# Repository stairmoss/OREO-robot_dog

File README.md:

# OREO – ROS Based Quadruped Robot Dog

# OREO V2 – ROS Powered Vision-Based Quadruped Robot  
### Hack Club Advanced Robotics Project

OREO V2 is a next-generation quadruped robot dog powered by a Raspberry Pi 4 and Teensy microcontroller, upgraded from the original ESP32 version into a full ROS-based intelligent robotic platform.

This version adds:

- 🧠 Computer Vision
- 🐾 12 High-Torque (20kg) Servos
- 🤖 ROS 2 Architecture
- 📡 Behavior-Based Control System
- ❤️ Touch Interaction
- 📷 Person Detection & Following

OREO V2 is no longer just a walking robot — it is an intelligent robotic companion platform built under a constrained $395 budget.

---

# 📌 Project Overview

| Item | Description |
|------|-------------|
| Robot Type | Quadruped (4-legged) |
| Architecture | ROS 2 Modular System |
| Main Computer | Raspberry Pi 4 Model B (4GB) |
| Motor Controller | Teensy Microcontroller |
| Servos per Leg | 3 (Hip, Upper, Knee) |
| Total Servos | 12 × 20kg High Torque |
| Sensors | IMU + Touch Sensor + Camera |
| Frame | 3D Printed Spot Micro Style |
| Power | 2S/3S Li-ion / LiPo Battery |
| Budget | ~$395 USD |
| Difficulty | Intermediate → Advanced |

---

# 🎯 Vision & Purpose

OREO V2 was built to:

- Transition from beginner robotics to ROS-based research structure
- Integrate computer vision into a quadruped platform
- Maintain affordability under strict budget constraints
- Build a modular robotic system expandable to SLAM and AI
- Learn real robotics engineering workflow

This robot is designed as a stepping stone toward advanced robotic systems.

---

# 🧠 System Architecture

OREO V2 uses a layered robotics architecture.

## 🔵 High-Level Control (Raspberry Pi 4)

Runs:

- Ubuntu 22.04 (64-bit)
- ROS 2 Humble
- OpenCV
- Behavior Node
- Gait Controller Node
- Vision Node

Responsibilities:

- Computer vision
- State machine decisions
- Gait generation
- Touch reaction logic
- Serial communication with Teensy

---

## 🟢 Low-Level Control (Teensy)

Responsibilities:

- Servo PWM generation via PCA9685
- Reading IMU data
- Executing joint commands
- Sending feedback (IMU + joint states)

Communication via USB Serial to Raspberry Pi.

---

# 🤖 ROS Node Structure

## 1️⃣ teensy_interface_node
- Converts ROS messages to serial packets
- Publishes:
  - `/joint_states`
  - `/imu`
- Subscribes:
  - `/joint_targets`

---

## 2️⃣ gait_controller_node
- Generates walking/trot gait
- Uses IMU feedback for balance correction
- Publishes `/joint_targets`

---

## 3️⃣ vision_node
- Captures camera feed
- Runs OpenCV person detection
- Publishes:
  - `/person_detected`
  - `/target_direction`

---

## 4️⃣ behavior_node (Robot Brain)

Handles states:

- IDLE
- SEARCH
- FOLLOW
- SIT
- HAPPY
- LOW_BATTERY

Input:
- Vision topic
- Touch topic
- Battery monitoring

Output:
- `/cmd_gait`
- Emotion state commands

---

## 5️⃣ touch_node
Reads capacitive or pressure sensor  
Publishes `/touch_event`  

When touched → Robot enters HAPPY state.

---

# ✨ Features

- 🐕 Full 12 DOF quadruped
- ⚙️ 20kg high torque servos
- 📷 Real-time person detection
- 🚶 Follow-human functionality
- ❤️ Touch-based interaction
- 📐 IMU-based balance correction
- 🔋 Dedicated high-current servo rail
- 🧩 Modular ROS architecture
- 🔌 Teensy real-time motor control
- 🧠 AI-expandable platform

---

# 🧩 Mechanical Design

Based on improved Spot Micro style frame.

## Body
- Central frame housing electronics
- Battery compartment protected
- Ventilation for Raspberry Pi
- Camera mount on head

## Legs
- 3 DOF per leg
- Parallel linkage for better weight distribution
- Reinforced servo mounts for 20kg servos
- Proper torque alignment to reduce mechanical stress

---

# 🔋 Power System

- 2S or 3S Li-ion pack
- High-current BEC or buck converter for servos (6V recommended)
- Separate regulated 5V rail for Raspberry Pi

⚠ Always:
- Measure voltage before connecting servos
- Test load voltage drop
- Never power servos directly from Raspberry Pi

---

# 🛠 Assembly Workflow

## Step 1 – 3D Print Parts
- Body frame
- Leg assemblies (×4)
- Head mount
- Internal mounting brackets

## Step 2 – Mount Servos
- Center all 12 servos before installation
- Attach horns at neutral 90°
- Secure using metal gears and lock screws

## Step 3 – Install Electronics
- Mount Raspberry Pi
- Mount Teensy
- Connect PCA9685
- Connect IMU
- Install touch sensor on head/body

## Step 4 – Wiring
- Servo power rail separated
- Signal wires routed cleanly
- Verify ground common between Teensy & Pi

## Step 5 – Software Setup
- Install Ubuntu on Pi
- Install ROS 2
- Clone project repository
- Build workspace using colcon
- Flash Teensy firmware
- Connect via USB

## Step 6 – Calibration
- Zero joint angles
- Adjust trim offsets
- Test single leg motion
- Test gait without load
- Then test full body

---

# 📦 Bill of Materials (Approx Budget)

| Component | Qty |
|-----------|-----|
| Raspberry Pi 4 (4GB) | 1 |
| Teensy Microcontroller | 1 |
| PCA9685 Servo Driver | 1 |
| 20kg Metal Gear Servos | 12 |
| IMU Sensor | 1 |
| Camera Module | 1 |
| Touch Sensor | 1 |
| Battery Pack | 1 |
| Buck Converter | 1 |
| 3D Printed Parts | 1 Set |
| Screws & Inserts | Set |

Total Estimated Cost: ~$390–395 USD

---

# 🚀 Software Capabilities

Current:

- Basic walk
- Trot gait
- Person detection
- Follow mode
- Touch reaction mode

Future Upgrades:

- SLAM
- Obstacle detection
- AI voice recognition
- Depth camera integration
- Web dashboard control

---

# 🏁 What Makes OREO V2 Special

- Built under strict budget
- Uses ROS (research-level framework)
- Integrates vision and behavior logic
- Maintains affordable hardware
- Fully modular and expandable
- Combines mechanical + electrical + software engineering

OREO V2 is not just a robot dog.

It is a robotics learning platform engineered for serious development while staying budget-conscious.

---

---

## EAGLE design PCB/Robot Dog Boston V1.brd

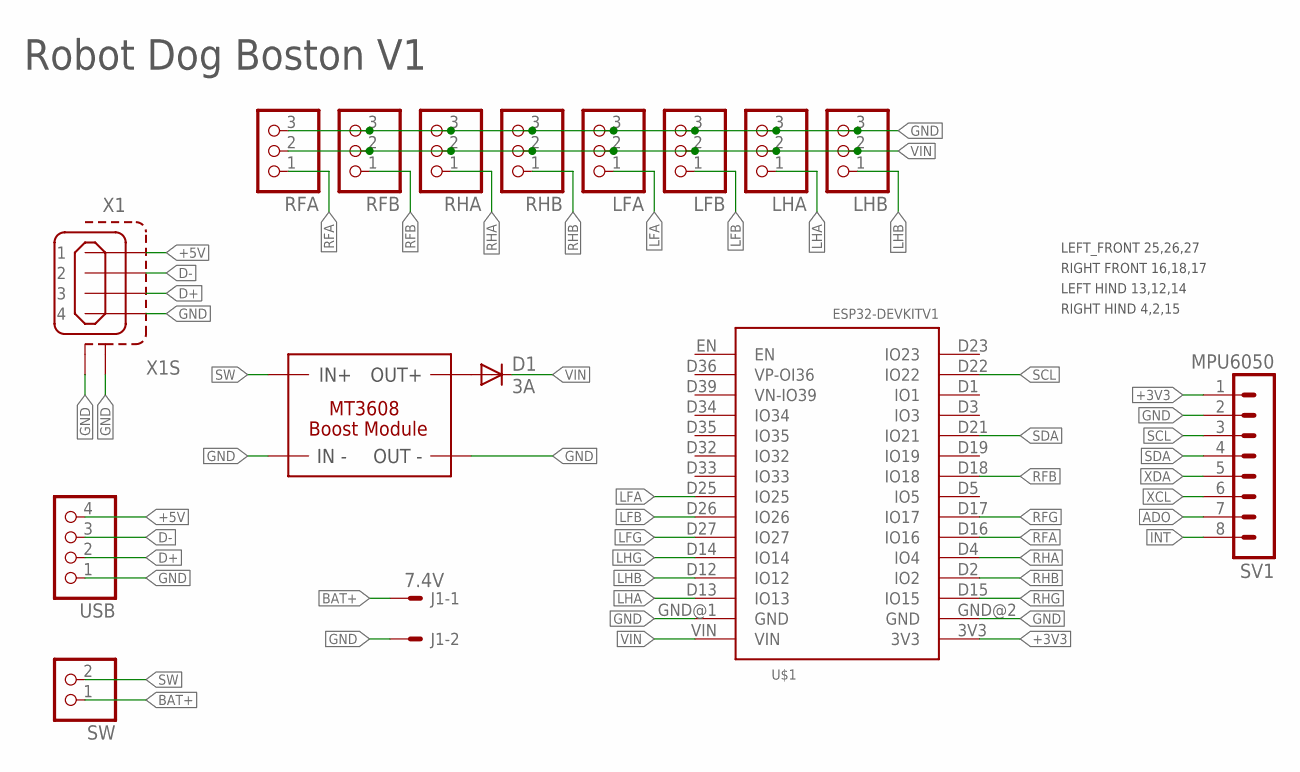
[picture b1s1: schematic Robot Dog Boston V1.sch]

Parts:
D1: 3A; DO15-12
J1: 7.4V; 7395-02
LFA: PINHD-1X3; 1X03
LFB: PINHD-1X3; 1X03
LHA: PINHD-1X3; 1X03
LHB: PINHD-1X3; 1X03
RFA: PINHD-1X3; 1X03
RFB: PINHD-1X3; 1X03
RHA: PINHD-1X3; 1X03
RHB: PINHD-1X3; 1X03
SV1: MPU6050; MA08-1
SW: PINHD-1X2; 1X02
U$1: ESP32DEVKITV1S; ESP32-DEVKIT1S
U$2: REGULATOR_MICRO15.4X9.4; 5V_REGULATOR_BOARD_MICRO_15_4_X_9_4
USB: PINHD-1X4/90; 1X04/90
X1: MINI-USB_SHIELD4P-85-32004-00X; 85-32004-00X

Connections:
+3V3: SV1.1, U$1.3V3
+5V: USB.4, X1.1
ADO: SV1.7
BAT+: J1.1, SW.1
D+: USB.2, X1.3
D-: USB.3, X1.2
GND: J1.2, LFA.3, LFB.3, LHA.3, LHB.3, RFA.3, RFB.3, RHA.3, RHB.3, SV1.2, U$1.GND@1 (GND), U$1.GND@2 (GND), U$2.IN-, U$2.OUT-, USB.1, X1.4, X1.M1 (S1), X1.M2 (S2)
INT: SV1.8
LFA: LFA.1, U$1.D25 (IO25)
LFB: LFB.1, U$1.D26 (IO26)
LFG: U$1.D27 (IO27)
LHA: LHA.1, U$1.D13 (IO13)
LHB: LHB.1, U$1.D12 (IO12)
LHG: U$1.D14 (IO14)
unnamed: D1.A, U$2.OUT+
RFA: RFA.1, U$1.D16 (IO16)
RFB: RFB.1, U$1.D18 (IO18)
RFG: U$1.D17 (IO17)
RHA: RHA.1, U$1.D4 (IO4)
RHB: RHB.1, U$1.D2 (IO2)
RHG: U$1.D15 (IO15)
SCL: SV1.3, U$1.D22 (IO22)
SDA: SV1.4, U$1.D21 (IO21)
SW: SW.2, U$2.IN+
VIN: D1.C, LFA.2, LFB.2, LHA.2, LHB.2, RFA.2, RFB.2, RHA.2, RHB.2, U$1.VIN
XCL: SV1.6
XDA: SV1.5

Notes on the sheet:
LEFT_FRONT 25,26,27
RIGHT FRONT 16,18,17
LEFT HIND 13,12,14
RIGHT HIND 4,2,15
Robot Dog Boston V1

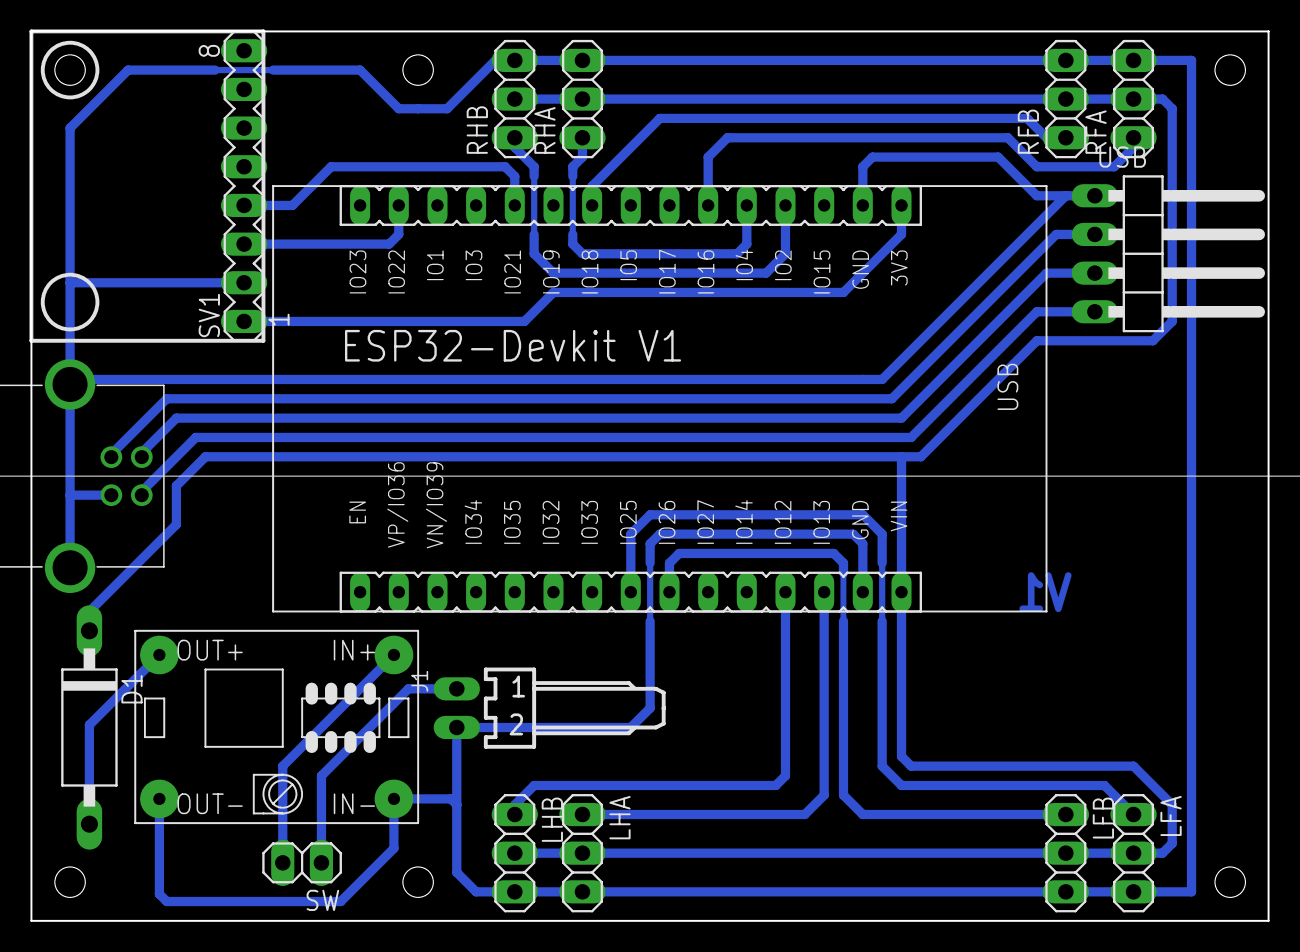
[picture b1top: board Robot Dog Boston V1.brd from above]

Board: 2 copper layers, 81.3 x 58.4 mm, 16 parts (0 on the bottom side), 19 nets.

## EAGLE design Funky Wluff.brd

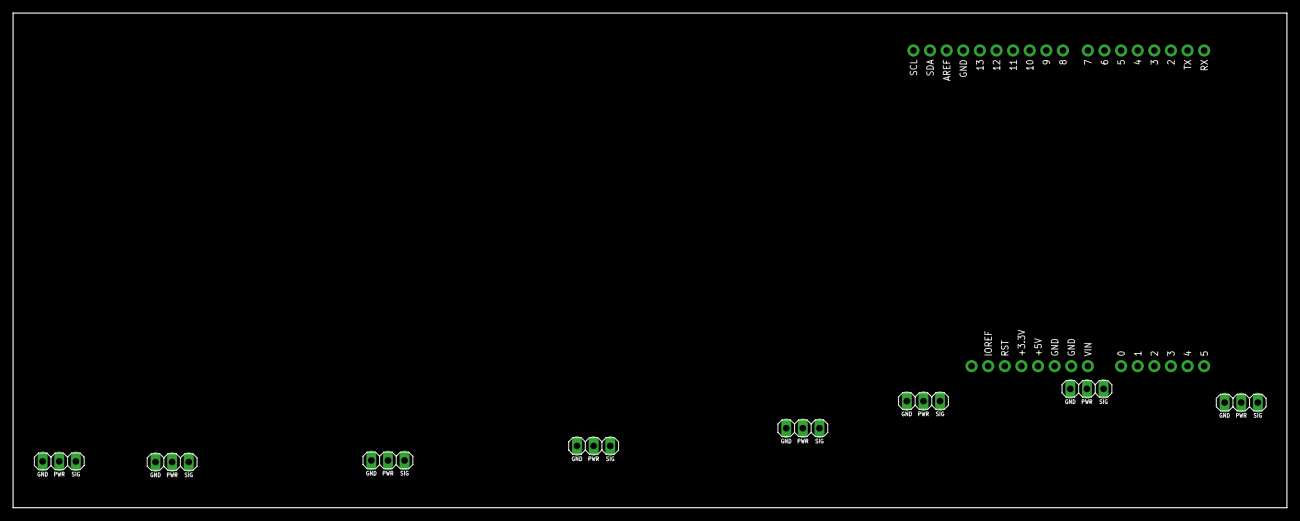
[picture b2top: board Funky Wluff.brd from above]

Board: 2 copper layers, 194.8 x 75.6 mm, 9 parts (0 on the bottom side), 10 nets, no tracks yet.

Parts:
SERVO1, SERVO2, SERVO3, SERVO4, SERVO5, SERVO6, SERVO7, SERVO8: SERVOSG90; SG90
U1: ARDUINO-UNO-R3-SHIELD

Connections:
U1_5V: SERVO1.2, SERVO2.2, SERVO3.2, SERVO4.2, SERVO5.2, SERVO6.2, SERVO7.2, SERVO8.2, U1.5V
U1_D6: SERVO2.3, U1.D6
U1_D7: SERVO1.3, U1.D7
U1_D8: SERVO8.3, U1.D8
U1_D9: SERVO7.3, U1.D9
U1_D10: SERVO6.3, U1.D10
U1_D11: SERVO5.3, U1.D11
U1_D12: SERVO4.3, U1.D12
U1_D13: SERVO3.3, U1.D13
U1_GND: SERVO1.1, SERVO2.1, SERVO3.1, SERVO4.1, SERVO5.1, SERVO6.1, SERVO7.1, SERVO8.1, U1.GND@0, U1.GND@1, U1.GND@2

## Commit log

2025-11-14 README.md
2025-12-17 circuit.brd
2025-12-25 Oreo robot dog project
    about the Oreo robot dog project, including design, assembly instructions, and components.
2025-12-25 Replace Hack Club banner and clean up README
    Updated Hack Club banner in README and fixed formatting.
2025-12-25 Add Hack Club logo to README conclusion
    Added Hack Club logo to the conclusion section.
2025-12-25 Add assembly guide for OREO robot dog
    This document provides a comprehensive guide on assembling the OREO robot dog, detailing the tools, parts checklist, and step-by-step instructions for assembly, wiring, and testing.
2025-12-30 Rename servo.ino to code/servo.ino
2026-01-19 Rename HAL.ino to code/HAL.ino
2026-01-19 Rename HAL_ESP32PWM.ino to code/HAL_ESP32PWM.ino
2026-01-19 Rename HAL_PCA9685.ino to code/HAL_PCA9685.ino
2026-01-19 Rename WiFi.ino to code/WiFi.ino
2026-01-19 Rename cli.h to code /cli.h
2026-01-19 Rename cli.ino to code /cli.ino
2026-01-19 Rename cliGet.ino to code /cliGet.ino
2026-01-19 Rename cliSet.ino to code /cliSet.ino
2026-01-19 Rename subscription.h to library/ subscription.h
2026-01-19 Rename config.h to library /config.h
2026-01-19 Rename config_small.h to library /config_small.h
2026-01-19 Rename def.h to library /def.h
2026-01-19 Rename config_wifi.example.h to library /config_wifi.example.h
2026-01-19 Rename cli.h to cli.h
2026-01-19 Rename failsafe.ino to code/failsafe.ino
2026-01-19 Rename gait.ino to code /gait.ino
2026-01-19 Rename helpers.ino to code /helpers.ino
2026-01-19 Rename i2cscan.ino to code /i2cscan.ino
2026-01-19 Rename imu.ino to code /imu.ino
2026-01-19 Rename packagesProcess.ino to code /packagesProcess.ino
2026-01-19 Rename powerSensor.ino to code /powerSensor.ino
2026-01-19 Rename robot_dog_esp32.ino to code /robot_dog_esp32.ino
2026-01-19 Rename settings.ino to code /settings.ino
2026-01-19 Rename subscription.ino to code /subscription.ino
2026-01-19 Rename testHAL.ino to code /testHAL.ino
2026-01-19 Rename webServer.ino to code /webServer.ino
2026-01-19 Rename Robot Dog Boston V1.brd to PCB/Robot Dog Boston V1.brd
2026-01-19 Rename Robot Dog Boston V1.kicad_prl to PCB /Robot Dog Boston V1.kicad_prl
2026-01-19 Rename Robot Dog Boston V1.kicad_pro to PCB /Robot Dog Boston V1.kicad_pro
2026-01-19 Rename Robot Dog Boston V1.sch to PCB /Robot Dog Boston V1.sch
2026-01-19 Revise README for OREO robot dog project
    Updated README to provide detailed project overview, features, assembly instructions, and BOM for the OREO quadruped robot dog.
2026-03-01 Revise README for OREO V2 ROS Quadruped Robot
    Updated project description and specifications for OREO V2, transitioning from ESP32 to ROS-based architecture with enhanced features.
2026-03-01 Rename index.html to stl file /index.html
2026-03-01 Convert BOM to CSV format
    Updated BOM format to use CSV standard with commas.
2026-03-01 Rename model (1).png to 3dpcbmodel.png
2026-03-01 Revise OREO V2 Assembly & Configuration Guide
    Updated assembly guide to focus on hardware assembly and wiring instructions for OREO V2. Revised sections for clarity and added detailed steps for mechanical build and wiring logic.
2026-04-23 Remove Hack Club banner from README
